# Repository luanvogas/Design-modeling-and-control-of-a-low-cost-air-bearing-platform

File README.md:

# Design, modeling, and control of a low-cost air-bearing platform

<div align="center">

This repository contains files produced as part of the doctoral thesis.

**Author:** Luan Mateus Bocalan Vogás  
**Advisor:** Prof. Dr. Roberto Kawakami Harrop Galvão  
**Co-Advisor:** Profa. Dra. Gabriela Werner Gabriel  

Instituto Tecnológico de Aeronáutica (ITA)  
Electronics Engineering Division  
São José dos Campos, SP, Brazil  
2026

</div>

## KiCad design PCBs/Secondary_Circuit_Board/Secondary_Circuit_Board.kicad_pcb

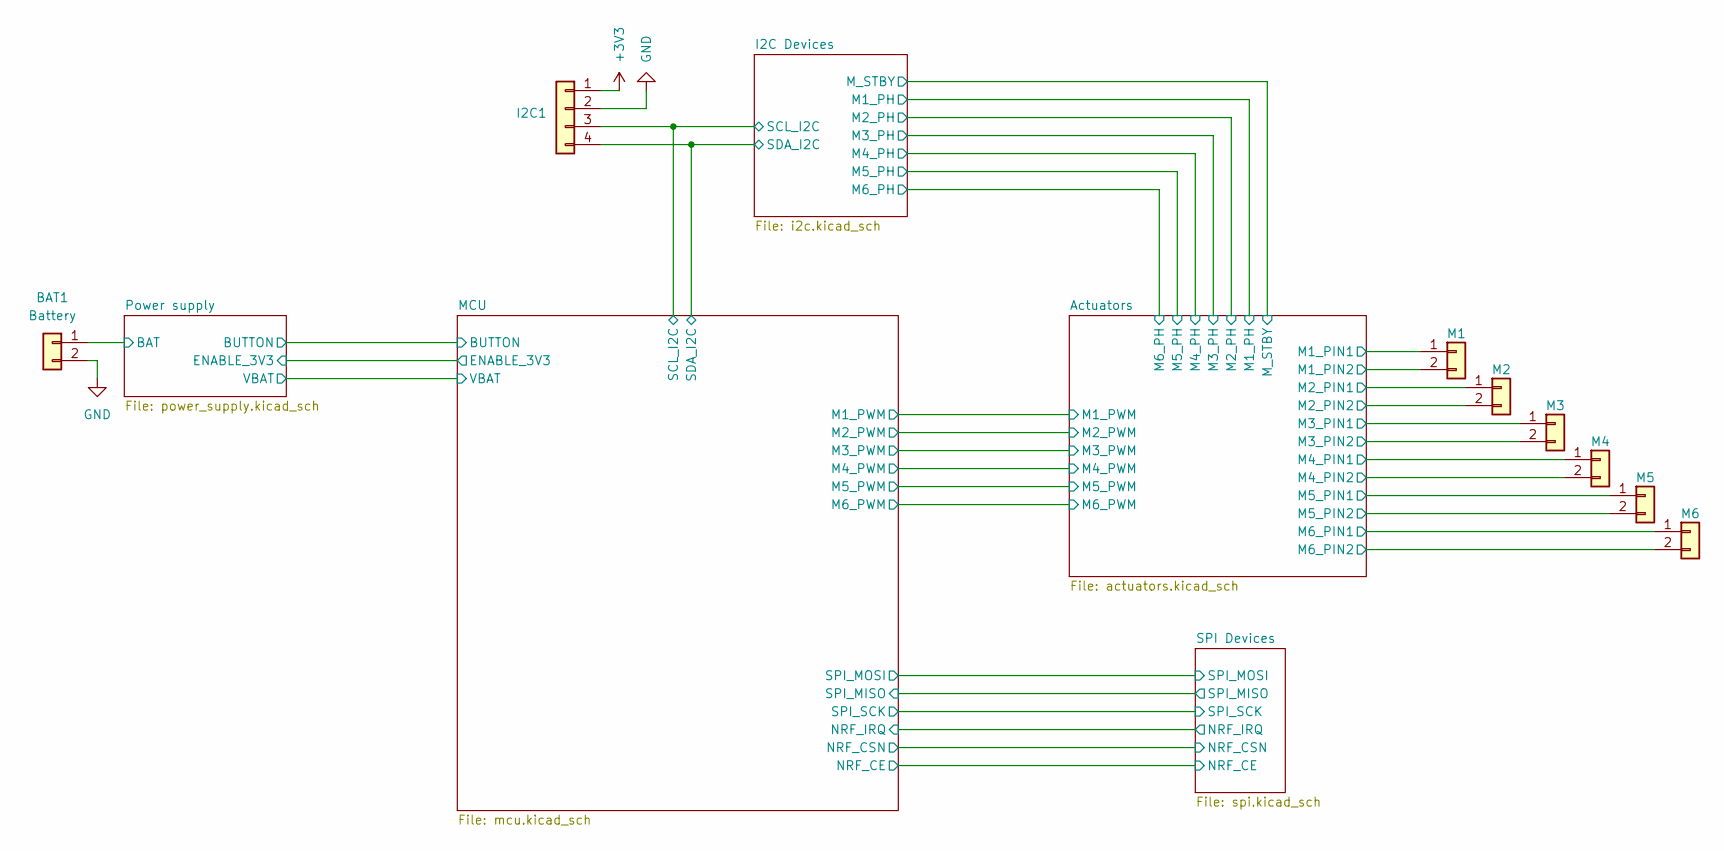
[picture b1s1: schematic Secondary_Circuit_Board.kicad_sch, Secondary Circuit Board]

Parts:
BAT1: Battery; PinHeader_1x02_P2.54mm_Horizontal
I2C1: I2C; JST_SH_BM04B-SRSS-TB_1x04-1MP_P1.00mm_Vertical
M1: M1; JST_SH_BM02B-SRSS-TB_1x02-1MP_P1.00mm_Vertical
M2: M2; JST_SH_BM02B-SRSS-TB_1x02-1MP_P1.00mm_Vertical
M3: M3; JST_SH_BM02B-SRSS-TB_1x02-1MP_P1.00mm_Vertical
M4: M4; JST_SH_BM02B-SRSS-TB_1x02-1MP_P1.00mm_Vertical
M5: M5; JST_SH_BM02B-SRSS-TB_1x02-1MP_P1.00mm_Vertical
M6: M6; JST_SH_BM02B-SRSS-TB_1x02-1MP_P1.00mm_Vertical

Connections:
+3V3: I2C1.1; also elsewhere on the board
/Actuators/M1_PIN1: M1.1; also elsewhere on the board
/Actuators/M1_PIN2: M1.2; also elsewhere on the board
/Actuators/M2_PIN1: M2.1; also elsewhere on the board
/Actuators/M2_PIN2: M2.2; also elsewhere on the board
/Actuators/M3_PIN1: M3.1; also elsewhere on the board
/Actuators/M3_PIN2: M3.2; also elsewhere on the board
/Actuators/M4_PIN1: M4.1; also elsewhere on the board
/Actuators/M4_PIN2: M4.2; also elsewhere on the board
/Actuators/M5_PIN1: M5.1; also elsewhere on the board
/Actuators/M5_PIN2: M5.2; also elsewhere on the board
/Actuators/M6_PIN1: M6.1; also elsewhere on the board
/Actuators/M6_PIN2: M6.2; also elsewhere on the board
/I2C Devices/SCL_I2C: I2C1.3; also elsewhere on the board
/I2C Devices/SDA_I2C: I2C1.4; also elsewhere on the board
GND: BAT1.2, I2C1.2; also elsewhere on the board
VCC: BAT1.1; also elsewhere on the board

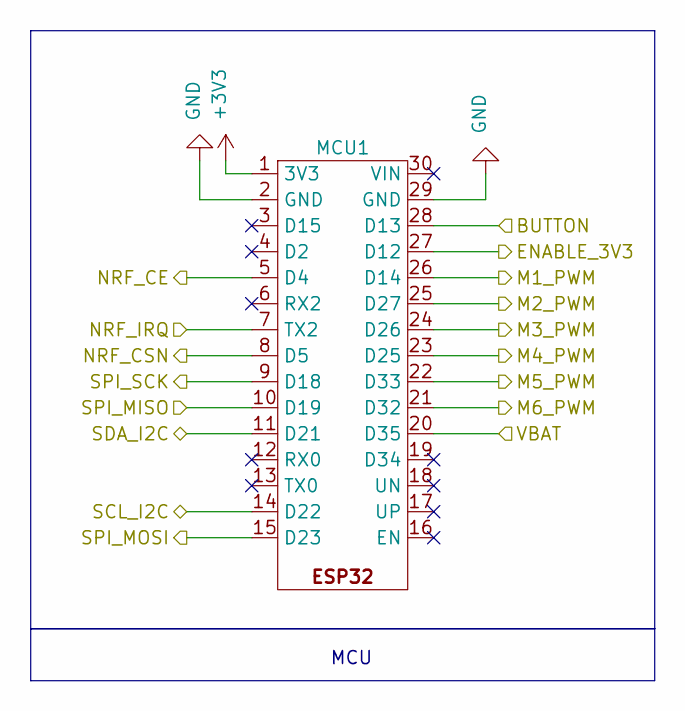
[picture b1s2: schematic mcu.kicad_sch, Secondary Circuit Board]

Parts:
MCU1: ESP32

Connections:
+3V3: MCU1.1 (3V3); also elsewhere on the board
/Actuators/M1_PWM: MCU1.26 (D14); also elsewhere on the board
/Actuators/M2_PWM: MCU1.25 (D27); also elsewhere on the board
/Actuators/M3_PWM: MCU1.24 (D26); also elsewhere on the board
/Actuators/M4_PWM: MCU1.23 (D25); also elsewhere on the board
/Actuators/M5_PWM: MCU1.22 (D33); also elsewhere on the board
/Actuators/M6_PWM: MCU1.21 (D32); also elsewhere on the board
/I2C Devices/SCL_I2C: MCU1.14 (D22); also elsewhere on the board
/I2C Devices/SDA_I2C: MCU1.11 (D21); also elsewhere on the board
/MCU/BUTTON: MCU1.28 (D13); also elsewhere on the board
/MCU/ENABLE_3V3: MCU1.27 (D12); also elsewhere on the board
/MCU/NRF_CE: MCU1.5 (D4); also elsewhere on the board
/MCU/NRF_CSN: MCU1.8 (D5); also elsewhere on the board
/MCU/NRF_IRQ: MCU1.7 (TX2); also elsewhere on the board
/MCU/SPI_MISO: MCU1.10 (D19); also elsewhere on the board
/MCU/SPI_MOSI: MCU1.15 (D23); also elsewhere on the board
/MCU/SPI_SCK: MCU1.9 (D18); also elsewhere on the board
/MCU/VBAT: MCU1.20 (D35); also elsewhere on the board
GND: MCU1.2 (GND), MCU1.29 (GND); also elsewhere on the board

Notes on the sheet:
MCU

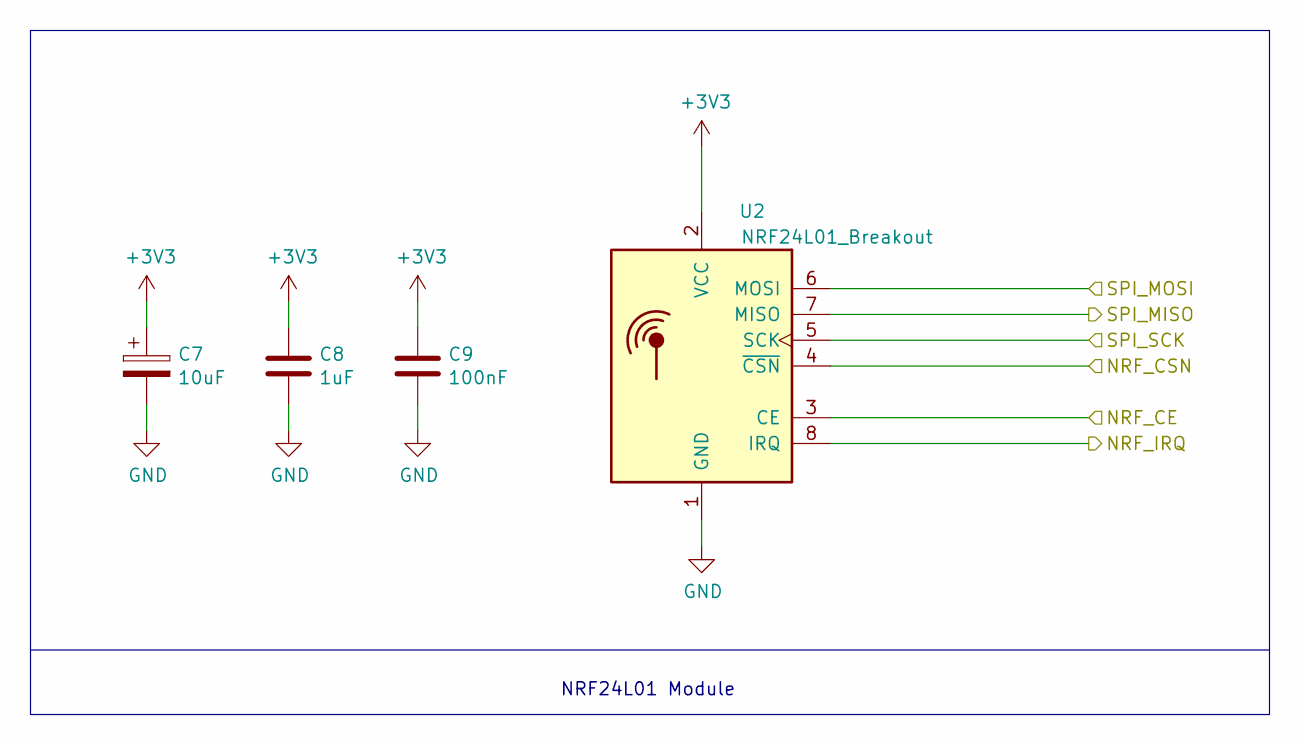
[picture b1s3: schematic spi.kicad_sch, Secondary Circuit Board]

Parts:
C7: 10uF; CP_EIA-3216-18_Kemet-A
C8: 1uF; C_1206_3216Metric
C9: 100nF; C_1206_3216Metric
U2: NRF24L01_Breakout; nRF24L01_Breakout

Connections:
+3V3: C7.1, C8.1, C9.1, U2.2 (VCC); also elsewhere on the board
/MCU/NRF_CE: U2.3 (CE); also elsewhere on the board
/MCU/NRF_CSN: U2.4 (~CSN); also elsewhere on the board
/MCU/NRF_IRQ: U2.8 (IRQ); also elsewhere on the board
/MCU/SPI_MISO: U2.7 (MISO); also elsewhere on the board
/MCU/SPI_MOSI: U2.6 (MOSI); also elsewhere on the board
/MCU/SPI_SCK: U2.5 (SCK); also elsewhere on the board
GND: C7.2, C8.2, C9.2, U2.1 (GND); also elsewhere on the board

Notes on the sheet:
NRF24L01 Module

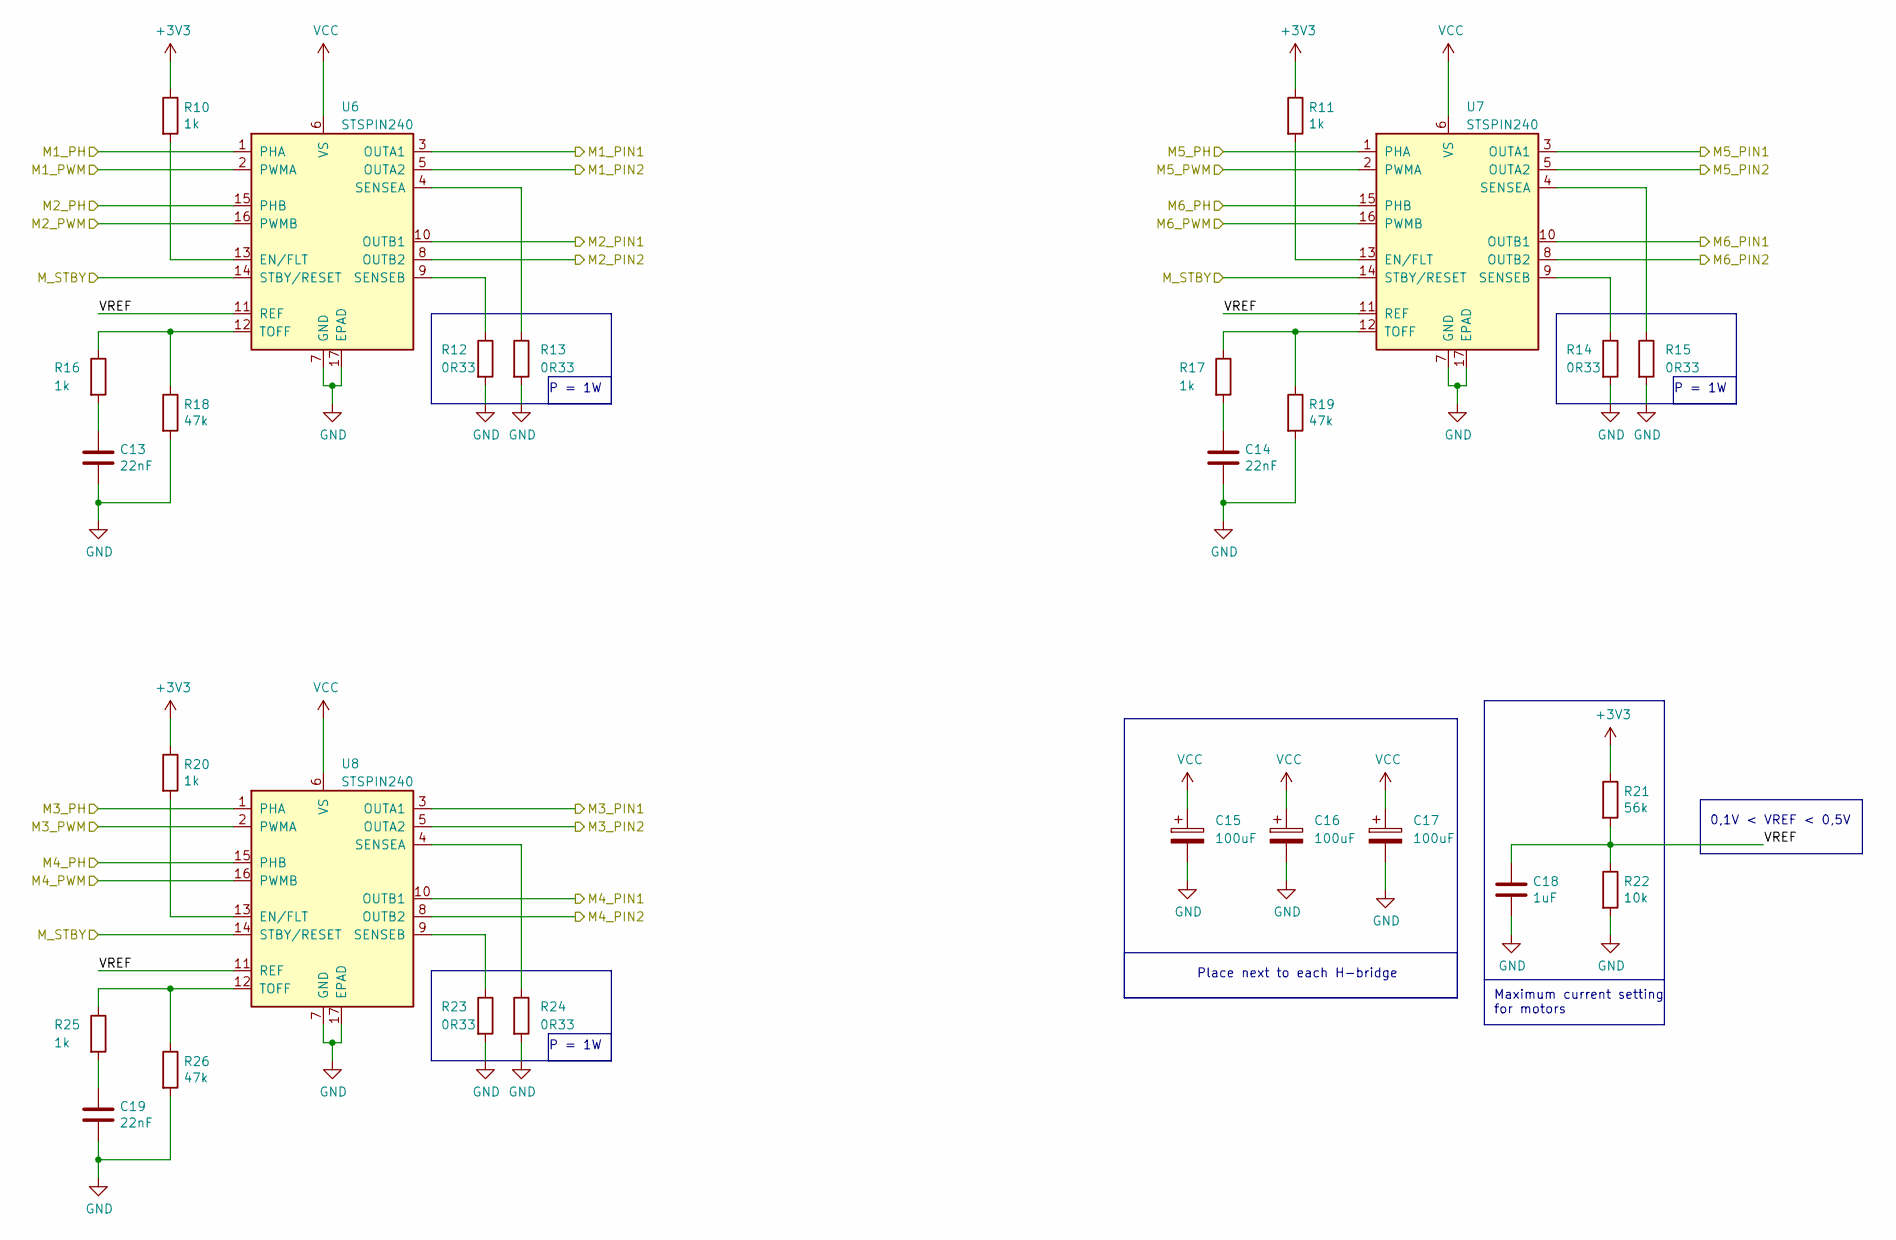
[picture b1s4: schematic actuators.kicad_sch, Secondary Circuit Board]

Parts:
C13, C14, C19: 22nF; C_1206_3216Metric
C15, C16, C17: 100uF; CP_Elec_6.3x7.7
C18: 1uF; C_1206_3216Metric
R10, R11, R16, R17, R20, R25: 1k; R_1206_3216Metric
R12, R13, R14, R15, R23, R24: 0R33; R_2512_6332Metric
R18, R19, R26: 47k; R_1206_3216Metric
R21: 56k; R_1206_3216Metric
R22: 10k; R_1206_3216Metric
U6, U7, U8: STSPIN240; PADS_COMPRIDOS_VQFN-16-1EP_3x3mm_P0.5mm_EP1.8x1.8mm

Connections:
+3V3: R10.1, R11.1, R20.1, R21.1; also elsewhere on the board
/Actuators/M1_PH: U6.1 (PHA); also elsewhere on the board
/Actuators/M1_PIN1: U6.3 (OUTA1); also elsewhere on the board
/Actuators/M1_PIN2: U6.5 (OUTA2); also elsewhere on the board
/Actuators/M1_PWM: U6.2 (PWMA); also elsewhere on the board
/Actuators/M2_PH: U6.15 (PHB); also elsewhere on the board
/Actuators/M2_PIN1: U6.10 (OUTB1); also elsewhere on the board
/Actuators/M2_PIN2: U6.8 (OUTB2); also elsewhere on the board
/Actuators/M2_PWM: U6.16 (PWMB); also elsewhere on the board
/Actuators/M3_PH: U8.1 (PHA); also elsewhere on the board
/Actuators/M3_PIN1: U8.3 (OUTA1); also elsewhere on the board
/Actuators/M3_PIN2: U8.5 (OUTA2); also elsewhere on the board
/Actuators/M3_PWM: U8.2 (PWMA); also elsewhere on the board
/Actuators/M4_PH: U8.15 (PHB); also elsewhere on the board
/Actuators/M4_PIN1: U8.10 (OUTB1); also elsewhere on the board
/Actuators/M4_PIN2: U8.8 (OUTB2); also elsewhere on the board
/Actuators/M4_PWM: U8.16 (PWMB); also elsewhere on the board
/Actuators/M5_PH: U7.1 (PHA); also elsewhere on the board
/Actuators/M5_PIN1: U7.3 (OUTA1); also elsewhere on the board
/Actuators/M5_PIN2: U7.5 (OUTA2); also elsewhere on the board
/Actuators/M5_PWM: U7.2 (PWMA); also elsewhere on the board
/Actuators/M6_PH: U7.15 (PHB); also elsewhere on the board
/Actuators/M6_PIN1: U7.10 (OUTB1); also elsewhere on the board
/Actuators/M6_PIN2: U7.8 (OUTB2); also elsewhere on the board
/Actuators/M6_PWM: U7.16 (PWMB); also elsewhere on the board
/Actuators/M_STBY: U6.14 (STBY/RESET), U7.14 (STBY/RESET), U8.14 (STBY/RESET); also elsewhere on the board
/Actuators/VREF: C18.1, R21.2, R22.1, U6.11 (REF), U7.11 (REF), U8.11 (REF)
GND: C13.2, C14.2, C15.2, C16.2, C17.2, C18.2, C19.2, R12.2, R13.2, R14.2, R15.2, R18.2, R19.2, R22.2, R23.2, R24.2, R26.2, U6.7 (GND), U6.17 (EPAD), U7.7 (GND), U7.17 (EPAD), U8.7 (GND), U8.17 (EPAD); also elsewhere on the board
unnamed: C13.1, R16.2
unnamed: C14.1, R17.2
unnamed: C19.1, R25.2
unnamed: R10.2, U6.13 (EN/FLT)
unnamed: R13.1, U6.4 (SENSEA)
unnamed: R12.1, U6.9 (SENSEB)
unnamed: R16.1, R18.1, U6.12 (TOFF)
unnamed: R11.2, U7.13 (EN/FLT)
unnamed: R15.1, U7.4 (SENSEA)
unnamed: R14.1, U7.9 (SENSEB)
unnamed: R17.1, R19.1, U7.12 (TOFF)
unnamed: R20.2, U8.13 (EN/FLT)
unnamed: R24.1, U8.4 (SENSEA)
unnamed: R23.1, U8.9 (SENSEB)
unnamed: R25.1, R26.1, U8.12 (TOFF)
VCC: C15.1, C16.1, C17.1, U6.6 (VS), U7.6 (VS), U8.6 (VS); also elsewhere on the board

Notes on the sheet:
0,1V < VREF < 0,5V
Maximum current setting for motors
P = 1W
Place next to each H-bridge

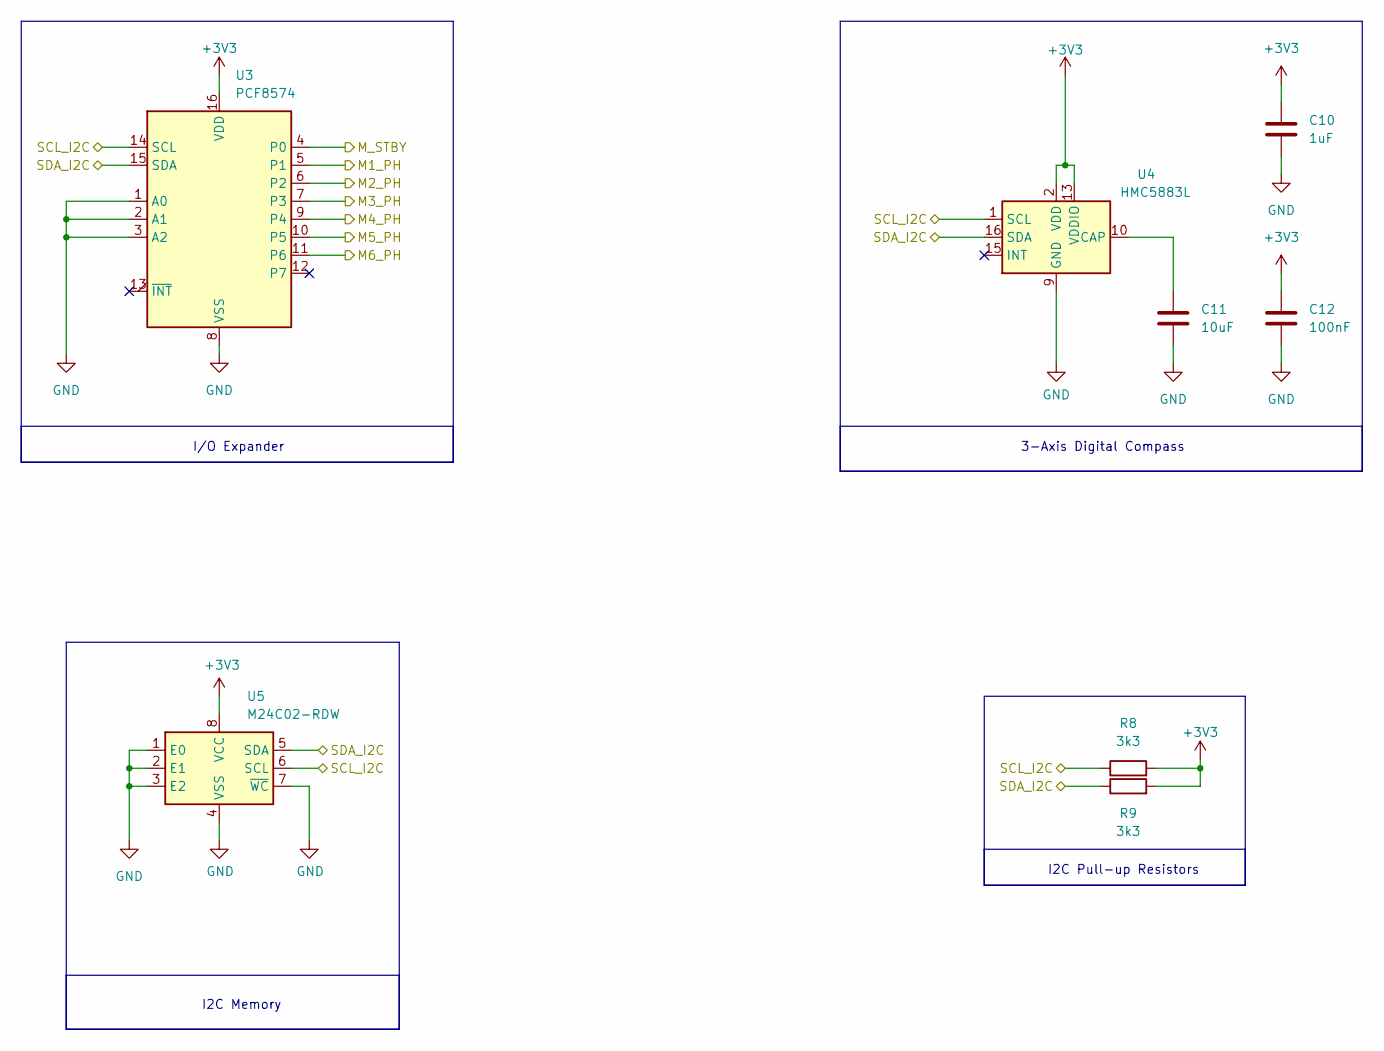
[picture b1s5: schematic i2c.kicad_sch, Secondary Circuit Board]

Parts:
C10: 1uF; C_1206_3216Metric
C11: 10uF; C_1206_3216Metric
C12: 100nF; C_1206_3216Metric
R8, R9: 3k3; R_1206_3216Metric
U3: PCF8574; SOIC-16W_7.5x12.8mm_P1.27mm
U4: HMC5883L; LGA-16_3x3mm_P0.5mm
U5: M24C02-RDW; TSSOP-8_4.4x3mm_P0.65mm

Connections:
+3V3: C10.1, C12.1, R8.2, R9.2, U3.16 (VDD), U4.2 (VDD), U4.13 (VDDIO), U5.8 (VCC); also elsewhere on the board
/Actuators/M1_PH: U3.5 (P1); also elsewhere on the board
/Actuators/M2_PH: U3.6 (P2); also elsewhere on the board
/Actuators/M3_PH: U3.7 (P3); also elsewhere on the board
/Actuators/M4_PH: U3.9 (P4); also elsewhere on the board
/Actuators/M5_PH: U3.10 (P5); also elsewhere on the board
/Actuators/M6_PH: U3.11 (P6); also elsewhere on the board
/Actuators/M_STBY: U3.4 (P0); also elsewhere on the board
/I2C Devices/SCL_I2C: R8.1, U3.14 (SCL), U4.1 (SCL), U5.6 (SCL); also elsewhere on the board
/I2C Devices/SDA_I2C: R9.1, U3.15 (SDA), U4.16 (SDA), U5.5 (SDA); also elsewhere on the board
GND: C10.2, C11.2, C12.2, U3.1 (A0), U3.2 (A1), U3.3 (A2), U3.8 (VSS), U4.9 (GND), U4.11 (GND), U5.1 (E0), U5.2 (E1), U5.3 (E2), U5.4 (VSS), U5.7 (~WC); also elsewhere on the board
unnamed: C11.1, U4.10 (CAP)

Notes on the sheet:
I2C Pull-up Resistors
I2C Memory
3-Axis Digital Compass
I/O Expander

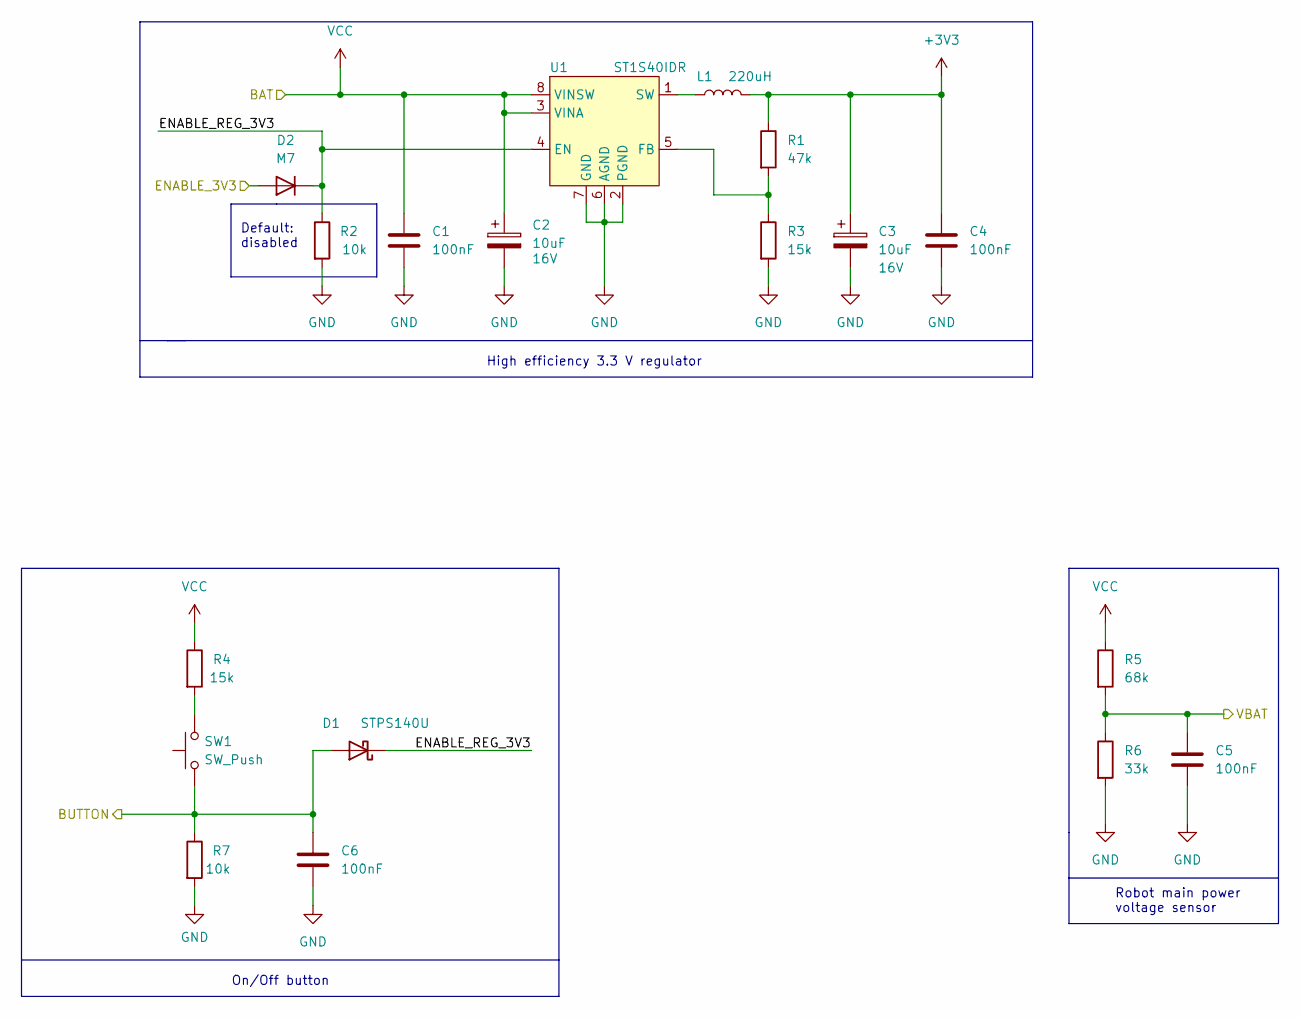
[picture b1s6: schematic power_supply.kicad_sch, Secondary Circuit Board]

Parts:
C1, C4, C5, C6: 100nF; C_1206_3216Metric
C2, C3: 10uF; CP_EIA-3216-18_Kemet-A_Pad1.58x1.35mm_HandSolder; Voltage 16V
D1: STPS140U; D_SMB
D2: M7; D_SMA
L1: 220uH; L_7.3x7.3_H4.5
R1: 47k; R_1206_3216Metric
R2, R7: 10k; R_1206_3216Metric
R3, R4: 15k; R_1206_3216Metric
R5: 68k; R_1206_3216Metric
R6: 33k; R_1206_3216Metric
SW1: SW_Push; SW_Push_1P1T_NO_CK_KMR2
U1: ST1S40IDR; SOIC-8_3.9x4.9mm_P1.27mm

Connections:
+3V3: C3.1, C4.1, L1.2, R1.1; also elsewhere on the board
/MCU/BUTTON: C6.1, D1.2 (A), R7.1, SW1.1; also elsewhere on the board
/MCU/ENABLE_3V3: D2.2 (A); also elsewhere on the board
/MCU/VBAT: C5.1, R5.2, R6.1; also elsewhere on the board
/Power supply/ENABLE_REG_3V3: D1.1 (K), D2.1 (K), R2.1, U1.4 (EN)
GND: C1.2, C2.2, C3.2, C4.2, C5.2, C6.2, R2.2, R3.2, R6.2, R7.2, U1.2 (PGND), U1.6 (AGND), U1.7 (GND); also elsewhere on the board
unnamed: R4.2, SW1.2
unnamed: R1.2, R3.1, U1.5 (FB)
unnamed: L1.1, U1.1 (SW)
VCC: C1.1, C2.1, R4.1, R5.1, U1.3 (VINA), U1.8 (VINSW); also elsewhere on the board

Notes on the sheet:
Default: disabled
High efficiency 3.3 V regulator
Robot main power voltage sensor
On/Off button

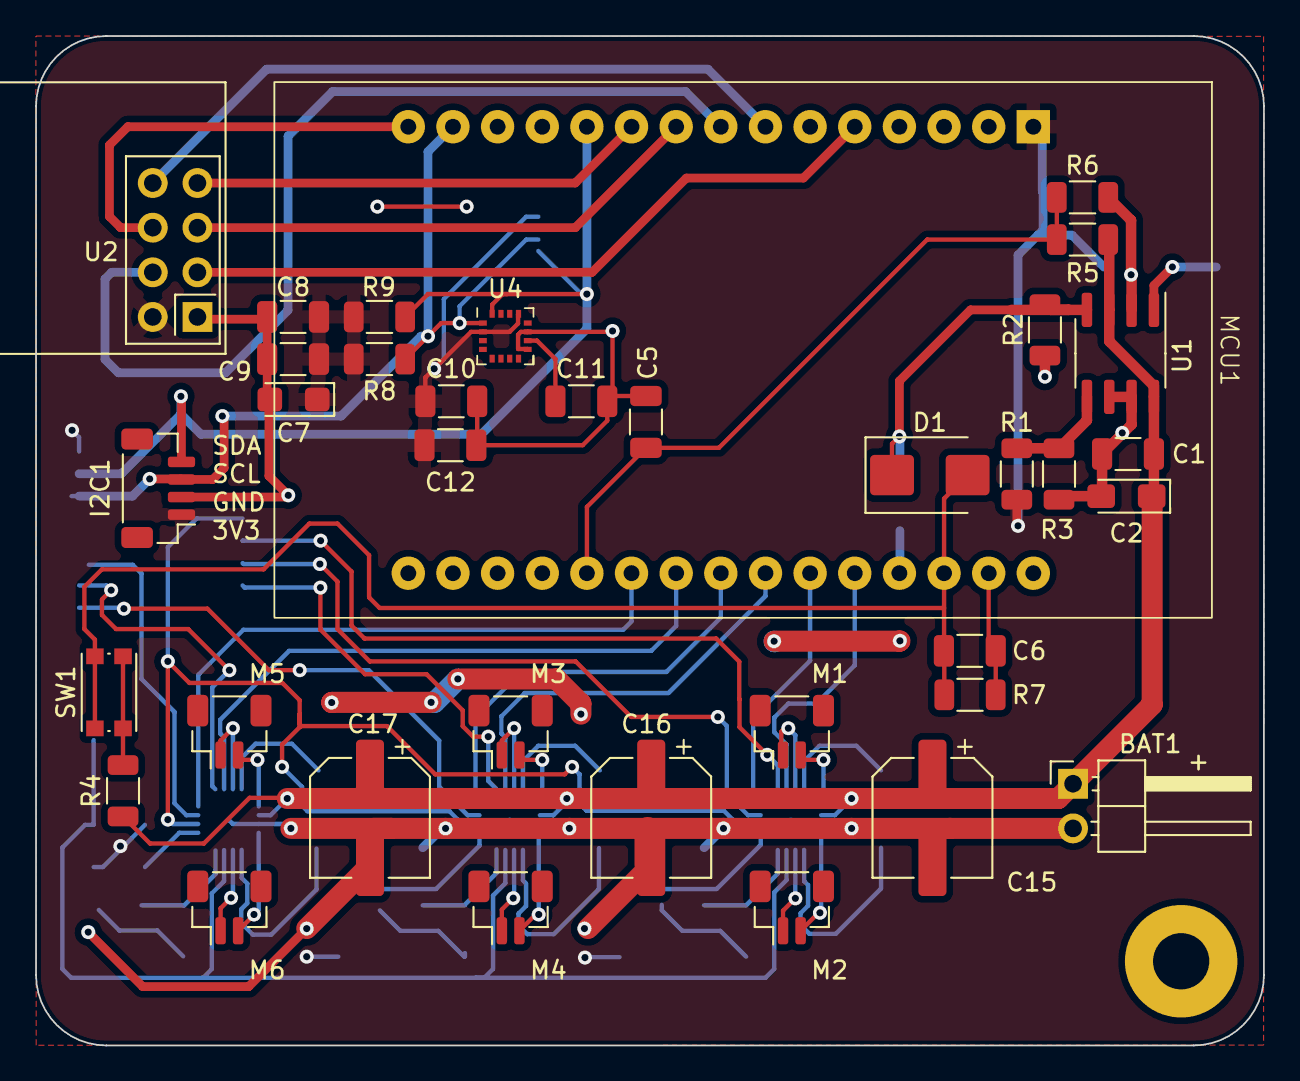
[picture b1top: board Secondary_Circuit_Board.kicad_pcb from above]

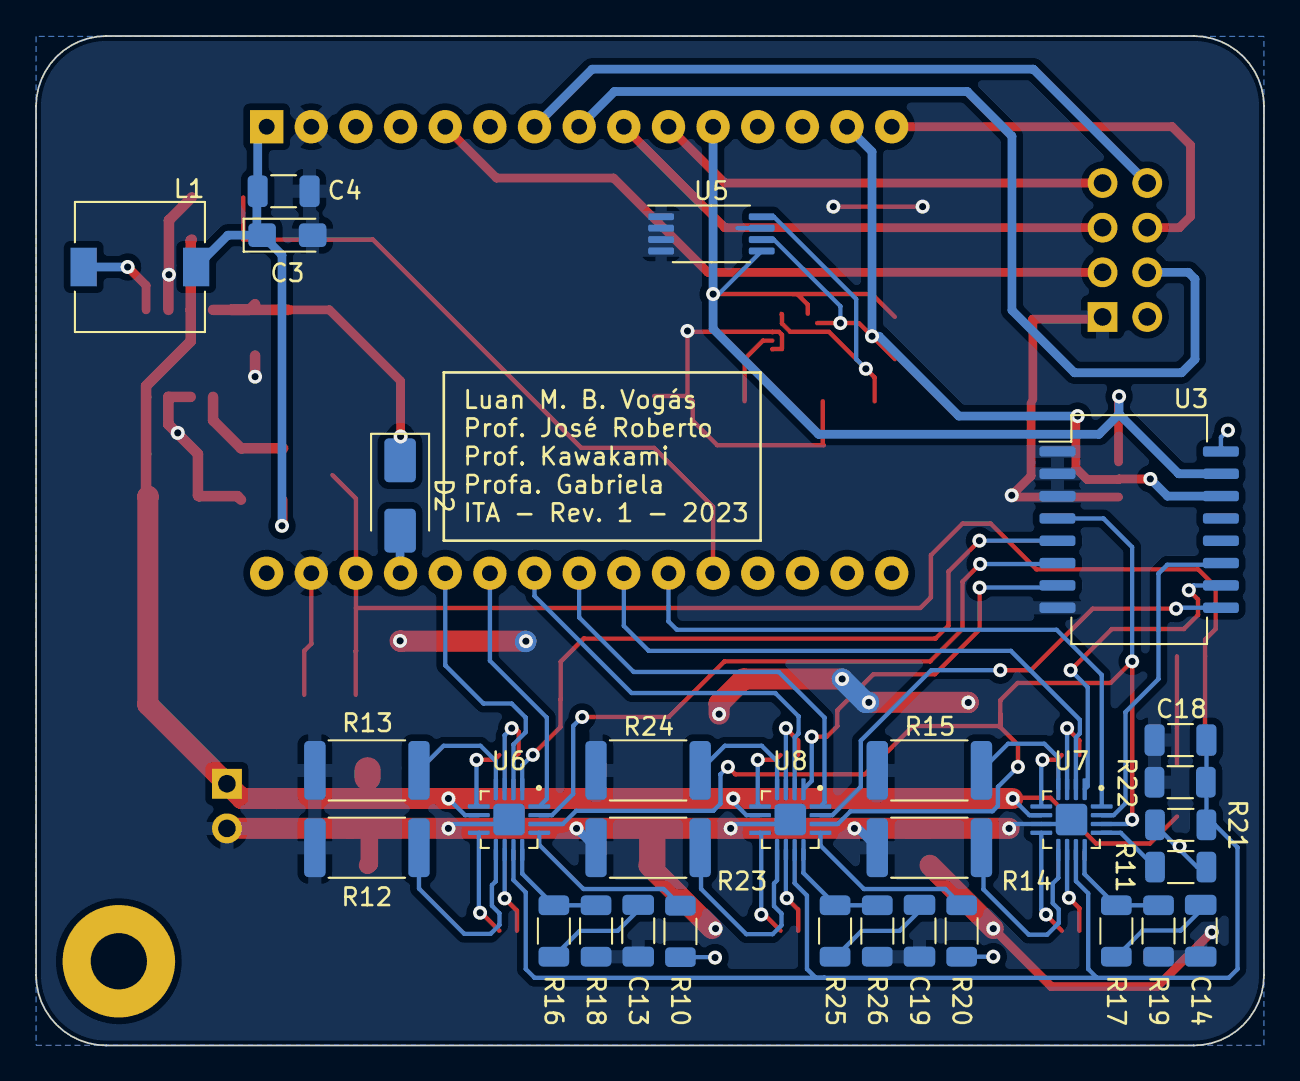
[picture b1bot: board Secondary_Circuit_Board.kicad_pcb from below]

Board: 2 copper layers, 69.9 x 57.4 mm, 66 parts (30 on the bottom side), 60 nets.

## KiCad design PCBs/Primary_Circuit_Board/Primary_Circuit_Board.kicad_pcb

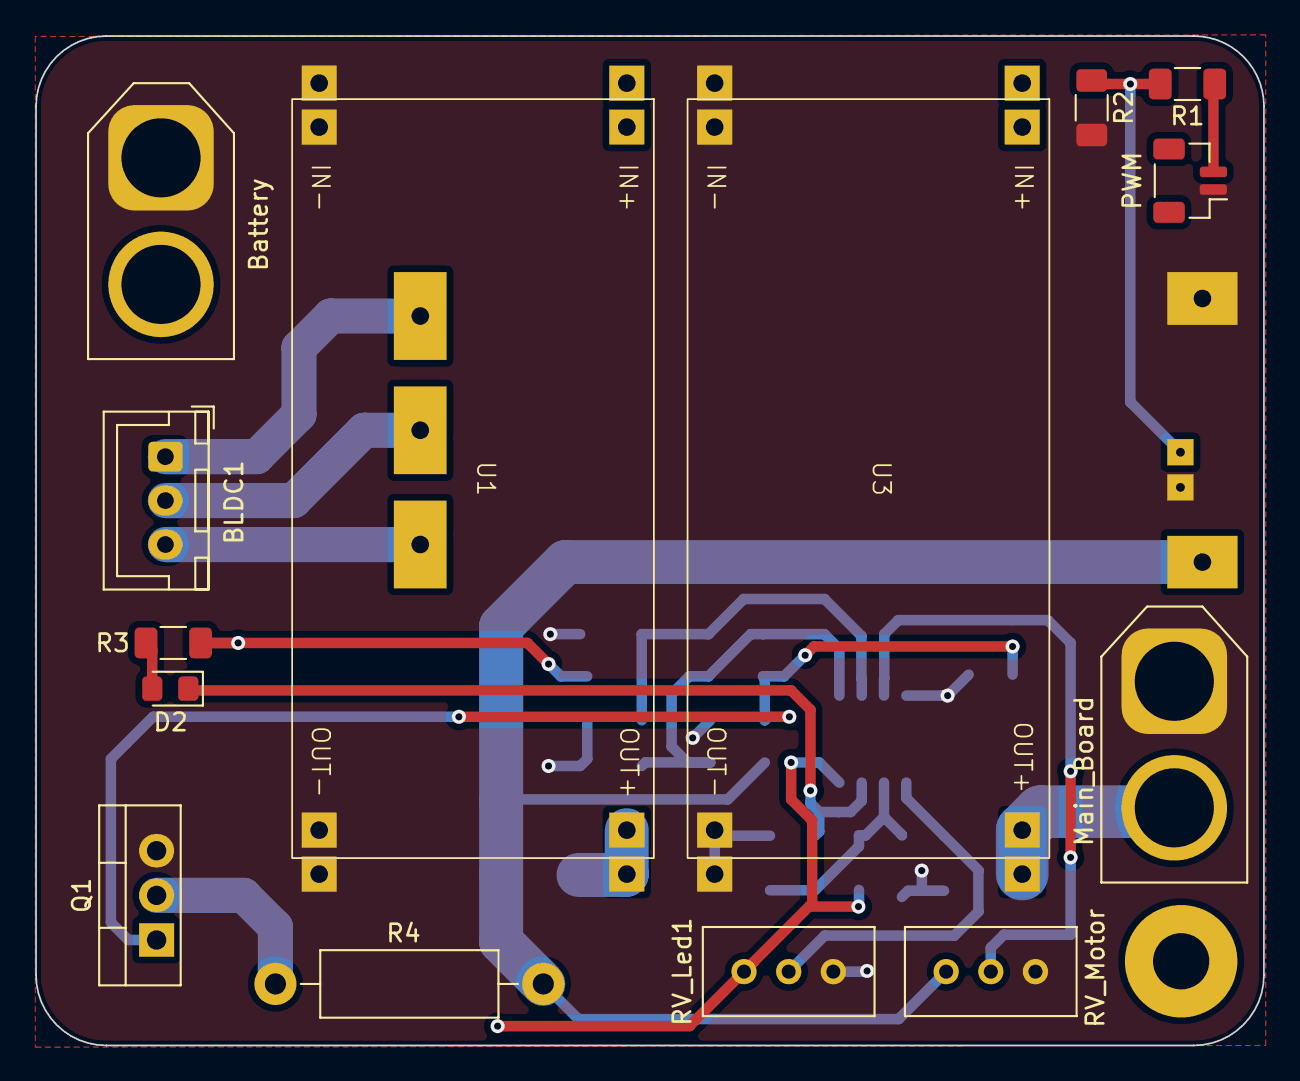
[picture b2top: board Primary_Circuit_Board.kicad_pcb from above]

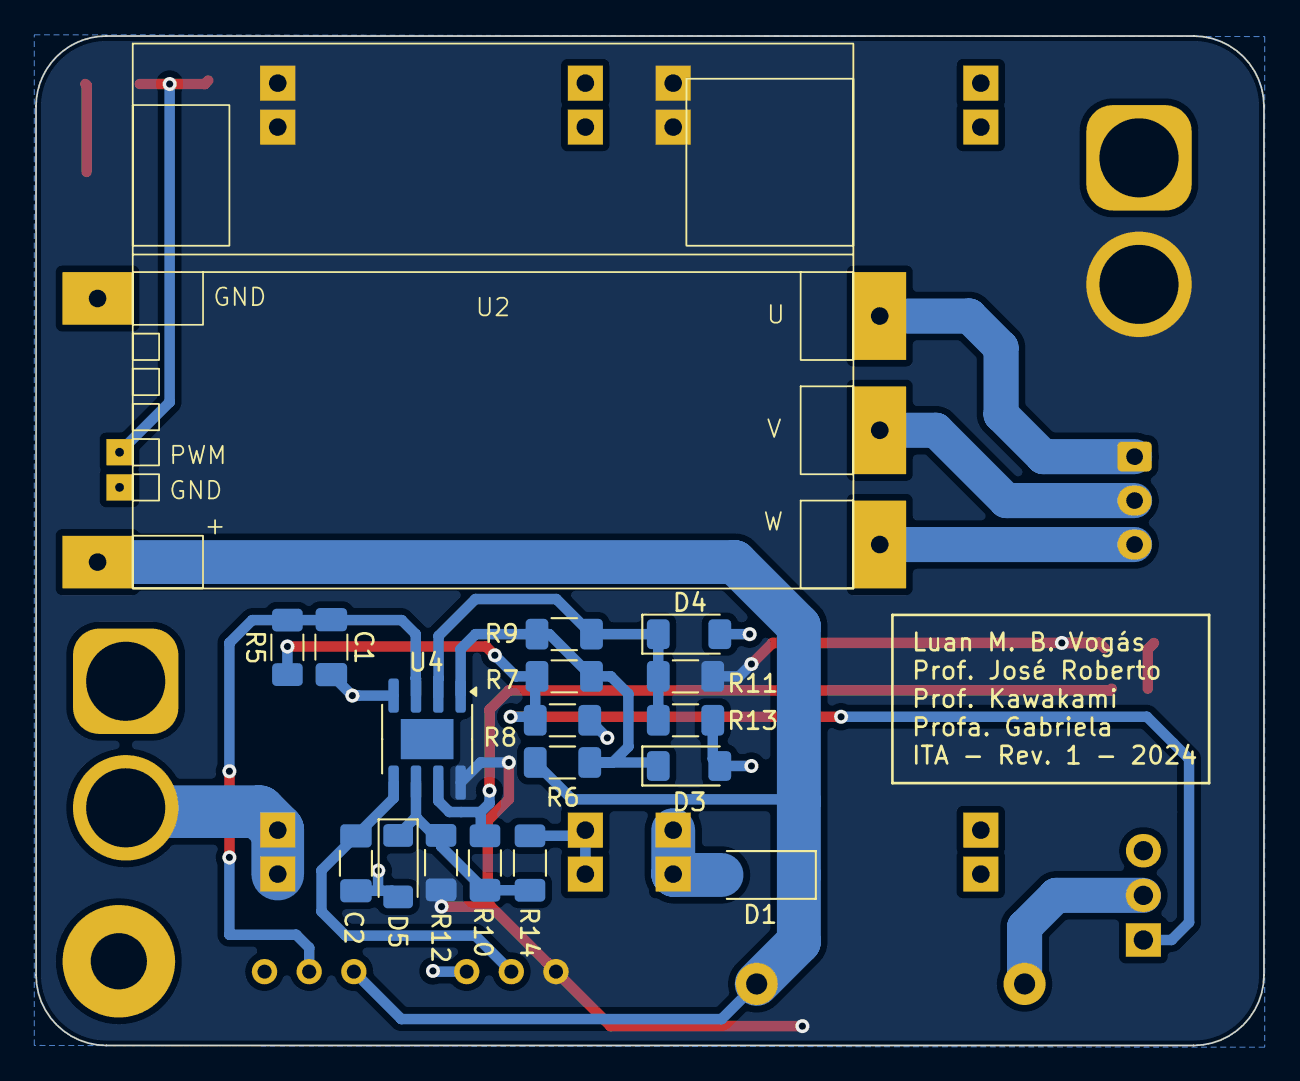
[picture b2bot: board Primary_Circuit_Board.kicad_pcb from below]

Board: 2 copper layers, 69.9 x 57.4 mm, 32 parts (18 on the bottom side), 19 nets.

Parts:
BLDC1: JST_XH_B3B-XH-A_1x03_P2.50mm_Vertical
Battery: Battery; AMASS_XT60-M_1x02_P7.20mm_Vertical
C1, C2: 100n; C_1206_3216Metric_Pad1.33x1.80mm_HandSolder
D1: STPS5H100AF; D_SOD-128
D2: LED; LED_0805_2012Metric_Pad1.15x1.40mm_HandSolder
D3: ZMM12; D_MiniMELF
D4, D5: ZMM3V3; D_MiniMELF
Main_Board: AMASS_XT60-F_1x02_P7.20mm_Vertical
PWM: JST_SH_BM02B-SRSS-TB_1x02-1MP_P1.00mm_Vertical
Q1: IRFZ44N; TO-220-3_Vertical
R1: 18k; R_1206_3216Metric_Pad1.30x1.75mm_HandSolder
R2, R8: 10k; R_1206_3216Metric_Pad1.30x1.75mm_HandSolder
R3: 470r; R_1206_3216Metric_Pad1.30x1.75mm_HandSolder
R4: 1r 1W; R_Axial_DIN0411_L9.9mm_D3.6mm_P15.24mm_Horizontal
R5, R9, R10, R13, R14: Reserved; R_1206_3216Metric_Pad1.30x1.75mm_HandSolder
R6: 1k; R_1206_3216Metric_Pad1.30x1.75mm_HandSolder
R7: 10r; R_1206_3216Metric_Pad1.30x1.75mm_HandSolder
R11, R12: 270r; R_1206_3216Metric_Pad1.30x1.75mm_HandSolder
RV_Led1: 10k; Potentiometer_Bourns_3296W_Vertical
RV_Motor: 10k; Potentiometer_Bourns_3296W_Vertical
U1, U3: XL6009_2A_Module
U2: B-G431B-ESC1
U4: LM393; SOIC-8-1EP_3.9x4.9mm_P1.27mm_EP2.29x3mm

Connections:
+12V: D1.1 (K), R4.1, R6.1, RV_Motor.1, U2.4 (+)
/Jumper: Q1.1 (G), R5.1, R7.1, R8.1
/Vbat: Battery.2, R3.1, R11.1, R12.1, RV_Led1.1, U1.1 (IN+), U3.1 (IN+), U4.8 (V+)
GND: Battery.1, C1.2, C2.2, D3.2 (A), D4.2 (A), D5.2 (A), Main_Board.1, PWM.1, Q1.3 (S), R2.2, R8.2, R13.2, R14.2, RV_Led1.3, RV_Motor.3, U1.2 (IN-), U1.3 (OUT-), U2.1 (GND), U2.3 (GND), U3.2 (IN-), U3.3 (OUT-), U4.4 (V-)
unnamed: BLDC1.1, U2.7 (U)
unnamed: BLDC1.2, U2.6 (V)
unnamed: BLDC1.3, U2.5 (W)
unnamed: D1.2 (A), U1.4 (OUT+)
unnamed: D2.2 (A), R3.2
unnamed: D2.1 (K), R10.2, U4.7
unnamed: D3.1 (K), R6.2, R7.2, R9.2, U4.1
unnamed: D4.1 (K), R9.1, R11.2, R13.1, U4.2 (-)
unnamed: D5.1 (K), R10.1, R12.2, R14.1, U4.6 (-)
unnamed: Main_Board.2, U3.4 (OUT+)
unnamed: PWM.2, R1.1
unnamed: Q1.2 (D), R4.2
unnamed: R1.2, R2.1, U2.2 (PWM)
unnamed: C1.1, R5.2, RV_Motor.2, U4.3 (+)
unnamed: C2.1, RV_Led1.2, U4.5 (+)
